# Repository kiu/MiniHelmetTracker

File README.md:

# MiniHelmetTracker

*MiniHelmetTracker* is a real-time standings table robot.

*MiniHelmetTracker* retrieves standings data - close to real-time - via WiFi and sorts [mini helmets](https://www.amazon.de/Riddell-8056173-NFL-32-teiliges-Helm-Tracker-Set/dp/B088W86SX4/) by league, conference, division or playoffs. A physical representation of the well known standings tables from [NFL](https://www.espn.com/nfl/standings) or [ESPN](https://www.espn.com/nfl/standings).

Checkout the [full story](https://schoar.de/tinkering/MiniHelmetTracker) or explore this repository including STL files, schematics, PCB layouts, firmware, server, etc.

# Youtube

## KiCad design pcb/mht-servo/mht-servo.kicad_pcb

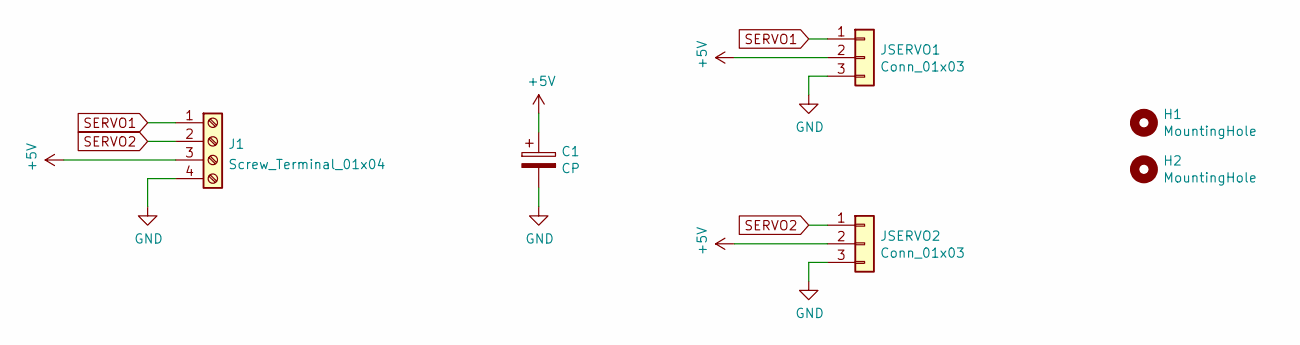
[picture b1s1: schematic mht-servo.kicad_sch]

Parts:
C1: CP; CP_Elec_8x10
H1, H2: MountingHole; MountingHole_3.2mm_M3
J1: Screw_Terminal_01x04; PinHeader_1x04_P2.54mm_Vertical
JSERVO1, JSERVO2: Conn_01x03; Pin_Header_Straight_1x03_Pitch2.54mm

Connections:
+5V: C1.1, J1.3, JSERVO1.2, JSERVO2.2
GND: C1.2, J1.4, JSERVO1.3, JSERVO2.3
SERVO1: J1.1, JSERVO1.1
SERVO2: J1.2, JSERVO2.1

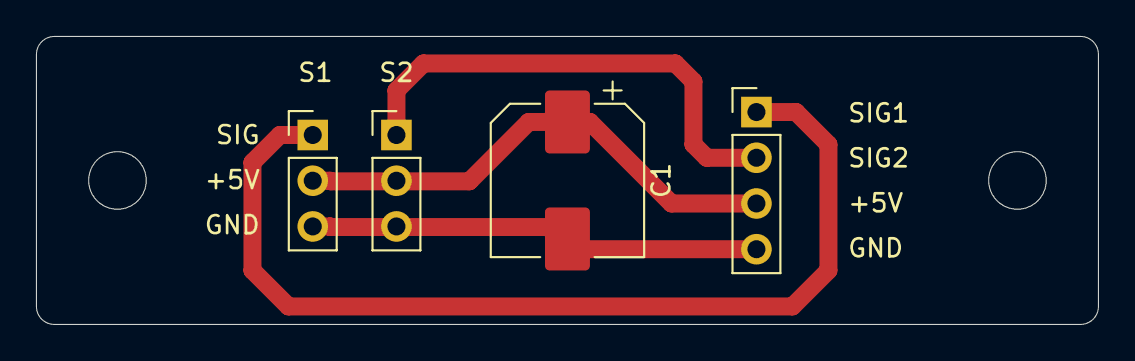
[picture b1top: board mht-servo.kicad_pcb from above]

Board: 2 copper layers, 59.0 x 16.0 mm, 6 parts (0 on the bottom side), 4 nets.

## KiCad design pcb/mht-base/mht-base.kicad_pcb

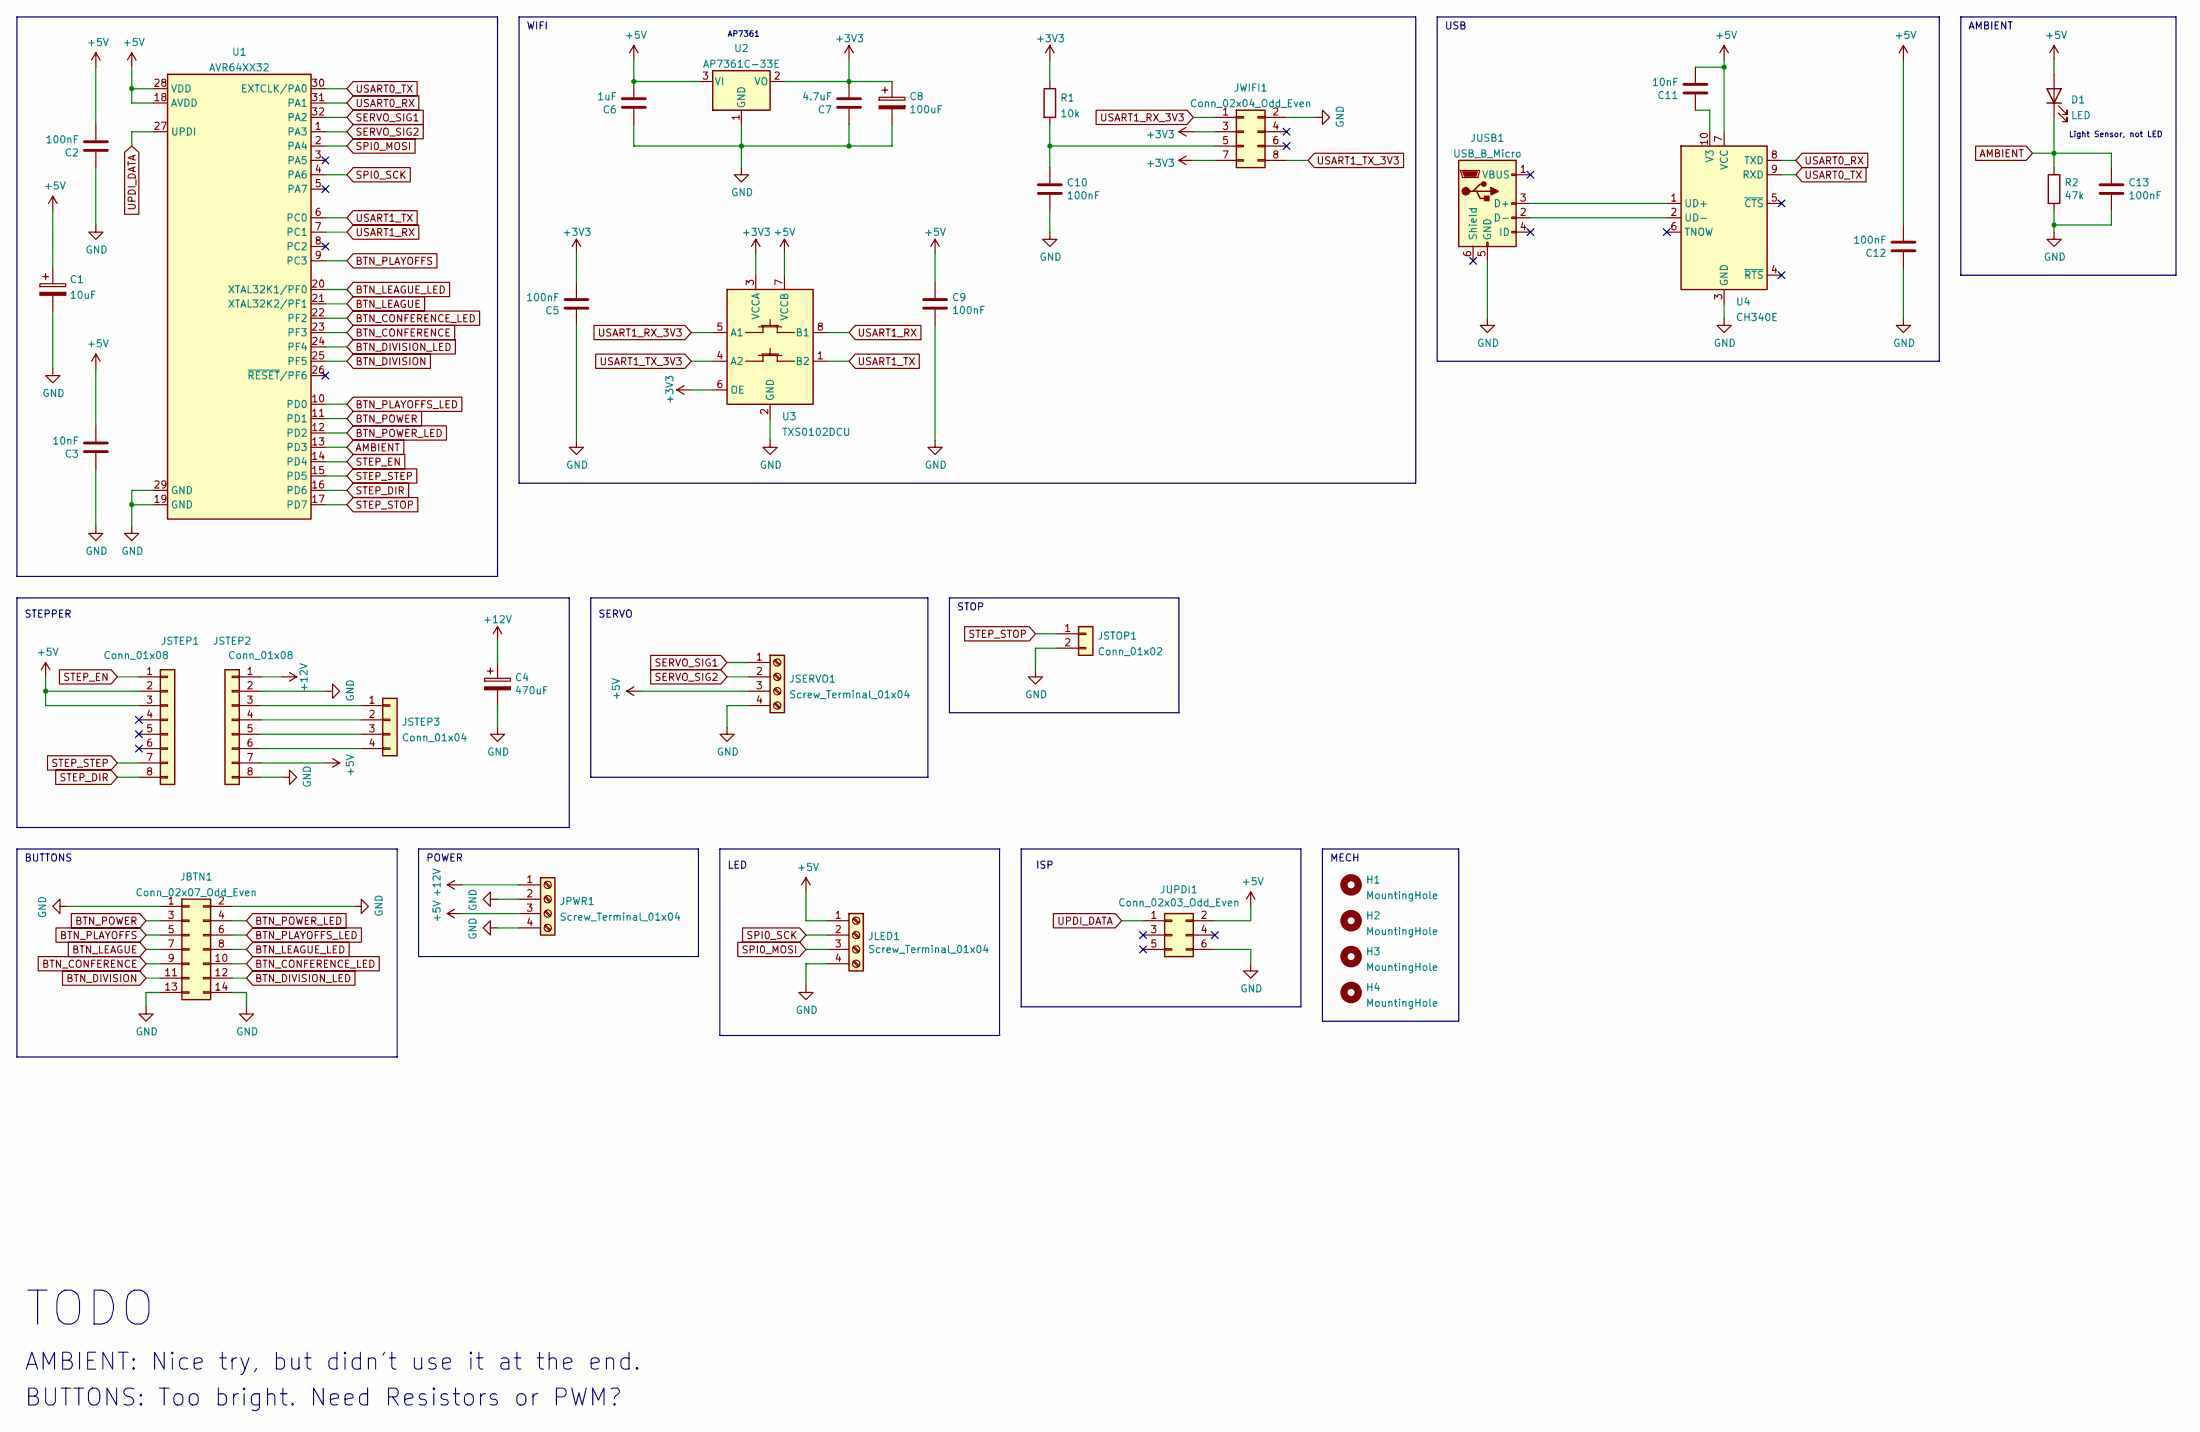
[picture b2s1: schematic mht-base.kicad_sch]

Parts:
C1: 10uF; CP_EIA-3216-18_Kemet-A
C2, C5, C9, C10, C12, C13: 100nF; C_0805_2012Metric
C3, C11: 10nF; C_0805_2012Metric
C4: 470uF; CP_Elec_8x10
C6: 1uF; C_0805_2012Metric
C7: 4.7uF; C_0805_2012Metric
C8: 100uF; CP_EIA-3528-21_Kemet-B
D1: LED; LED_D5.0mm
H1, H2, H3, H4: MountingHole; MountingHole_3.2mm_M3
JBTN1: Conn_02x07_Odd_Even; IDC-Header_2x07_P2.54mm_Vertical
JLED1: Screw_Terminal_01x04; TerminalBlock_RND_205-00047_1x04_P5.00mm_Horizontal
JPWR1: Screw_Terminal_01x04; TerminalBlock_RND_205-00047_1x04_P5.00mm_Horizontal
JSERVO1: Screw_Terminal_01x04; TerminalBlock_RND_205-00047_1x04_P5.00mm_Horizontal
JSTEP1, JSTEP2: Conn_01x08; PinSocket_1x08_P2.54mm_Vertical
JSTEP3: Conn_01x04; PinHeader_1x04_P2.54mm_Vertical
JSTOP1: Conn_01x02; TerminalBlock_RND_205-00012_1x02_P5.00mm_Horizontal
JUPDI1: Conn_02x03_Odd_Even; IDC-Header_2x03_P2.54mm_Vertical
JUSB1: USB_B_Micro; GCT-USB3076-30-A
JWIFI1: Conn_02x04_Odd_Even; PinHeader_2x04_P2.54mm_Vertical
R1: 10k; R_0805_2012Metric
R2: 47k; R_0805_2012Metric
U1: AVR64XX32; TQFP-32_7x7mm_P0.8mm
U2: AP7361C-33E; SOT-223-3_TabPin2
U3: TXS0102DCU; VSSOP-8_2.3x2mm_P0.5mm
U4: CH340E; MSOP-10_3x3mm_P0.5mm

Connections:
+3V3: C5.2, C7.2, C8.1, JWIFI1.3, JWIFI1.7, R1.1, U2.2 (VO), U3.3 (VCCA), U3.6 (OE)
+5V: C1.1, C2.2, C3.2, C6.2, C9.1, C11.2, C12.2, D1.2 (A), JLED1.1, JPWR1.3, JSERVO1.3, JSTEP1.2, JSTEP1.3, JSTEP2.7, JUPDI1.2, U1.18 (AVDD), U1.28 (VDD), U2.3 (VI), U3.7 (VCCB), U4.7 (VCC)
+12V: C4.1, JPWR1.1, JSTEP2.1
AMBIENT: C13.1, D1.1 (K), R2.1, U1.13 (PD3)
BTN_CONFERENCE: JBTN1.9, U1.23 (PF3)
BTN_CONFERENCE_LED: JBTN1.10, U1.22 (PF2)
BTN_DIVISION: JBTN1.11, U1.25 (PF5)
BTN_DIVISION_LED: JBTN1.12, U1.24 (PF4)
BTN_LEAGUE: JBTN1.7, U1.21 (XTAL32K2/PF1)
BTN_LEAGUE_LED: JBTN1.8, U1.20 (XTAL32K1/PF0)
BTN_PLAYOFFS: JBTN1.5, U1.9 (PC3)
BTN_PLAYOFFS_LED: JBTN1.6, U1.10 (PD0)
BTN_POWER: JBTN1.3, U1.11 (PD1)
BTN_POWER_LED: JBTN1.4, U1.12 (PD2)
GND: C1.2, C2.1, C3.1, C4.2, C5.1, C6.1, C7.1, C8.2, C9.2, C10.2, C12.1, C13.2, JBTN1.1, JBTN1.2, JBTN1.13, JBTN1.14, JLED1.4, JPWR1.2, JPWR1.4, JSERVO1.4, JSTEP2.2, JSTEP2.8, JSTOP1.2, JUPDI1.6, JUSB1.5 (GND), JWIFI1.2, R2.2, U1.19 (GND), U1.29 (GND), U2.1 (GND), U3.2 (GND), U4.3 (GND)
unnamed: C10.1, JWIFI1.5, R1.2
unnamed: C11.1, U4.10 (V3)
unnamed: JSTEP2.3, JSTEP3.1
unnamed: JSTEP2.4, JSTEP3.2
unnamed: JSTEP2.5, JSTEP3.3
unnamed: JSTEP2.6, JSTEP3.4
unnamed: JUSB1.2 (D-), U4.2 (UD-)
unnamed: JUSB1.3 (D+), U4.1 (UD+)
SERVO_SIG1: JSERVO1.1, U1.32 (PA2)
SERVO_SIG2: JSERVO1.2, U1.1 (PA3)
SPI0_MOSI: JLED1.3, U1.2 (PA4)
SPI0_SCK: JLED1.2, U1.4 (PA6)
STEP_DIR: JSTEP1.8, U1.16 (PD6)
STEP_EN: JSTEP1.1, U1.14 (PD4)
STEP_STEP: JSTEP1.7, U1.15 (PD5)
STEP_STOP: JSTOP1.1, U1.17 (PD7)
UPDI_DATA: JUPDI1.1, U1.27 (UPDI)
USART0_RX: U1.31 (PA1), U4.8 (TXD)
USART0_TX: U1.30 (EXTCLK/PA0), U4.9 (RXD)
USART1_RX: U1.7 (PC1), U3.8 (B1)
USART1_RX_3V3: JWIFI1.1, U3.5 (A1)
USART1_TX: U1.6 (PC0), U3.1 (B2)
USART1_TX_3V3: JWIFI1.8, U3.4 (A2)

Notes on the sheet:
TODO
USB
AMBIENT
LED
BUTTONS
STOP
WIFI
POWER
MECH
ISP
AP7361
STEPPER
AMBIENT: Nice try, but didn't use it at the end.
SERVO
Light Sensor, not LED
BUTTONS: Too bright. Need Resistors or PWM?

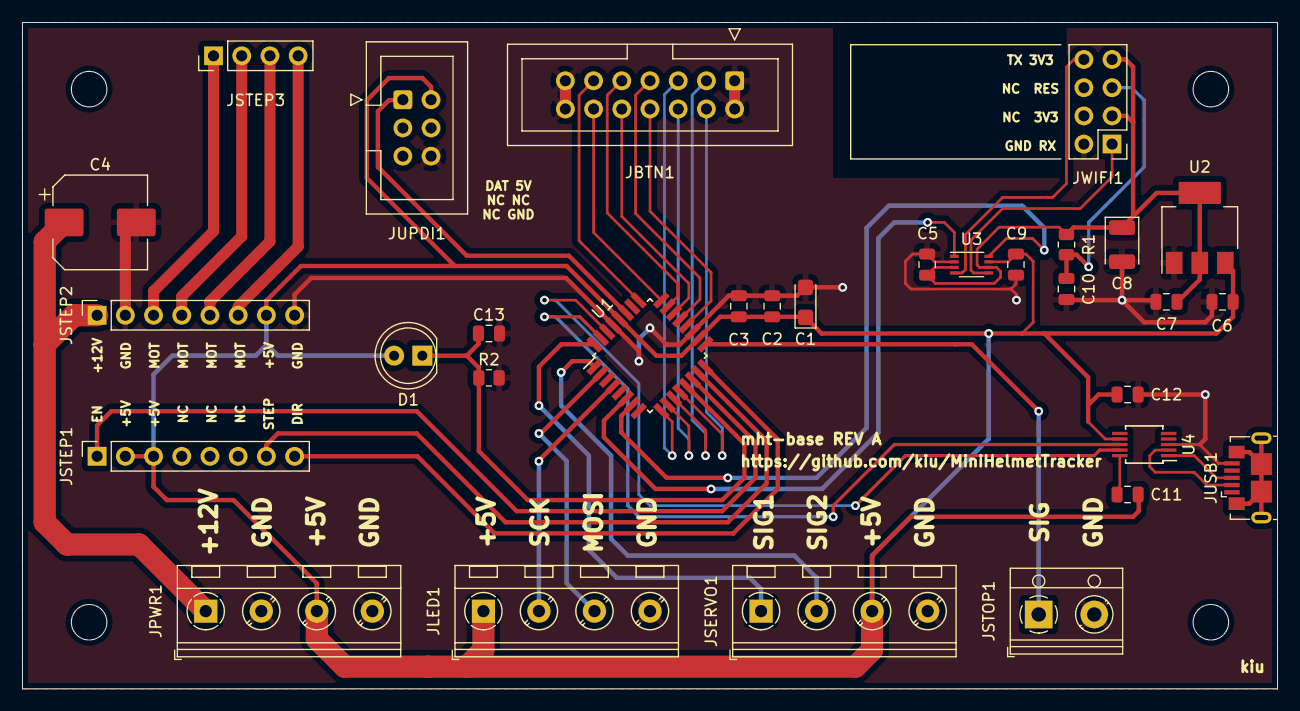
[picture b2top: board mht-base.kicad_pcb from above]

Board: 2 copper layers, 113.0 x 60.0 mm, 35 parts (0 on the bottom side), 38 nets.

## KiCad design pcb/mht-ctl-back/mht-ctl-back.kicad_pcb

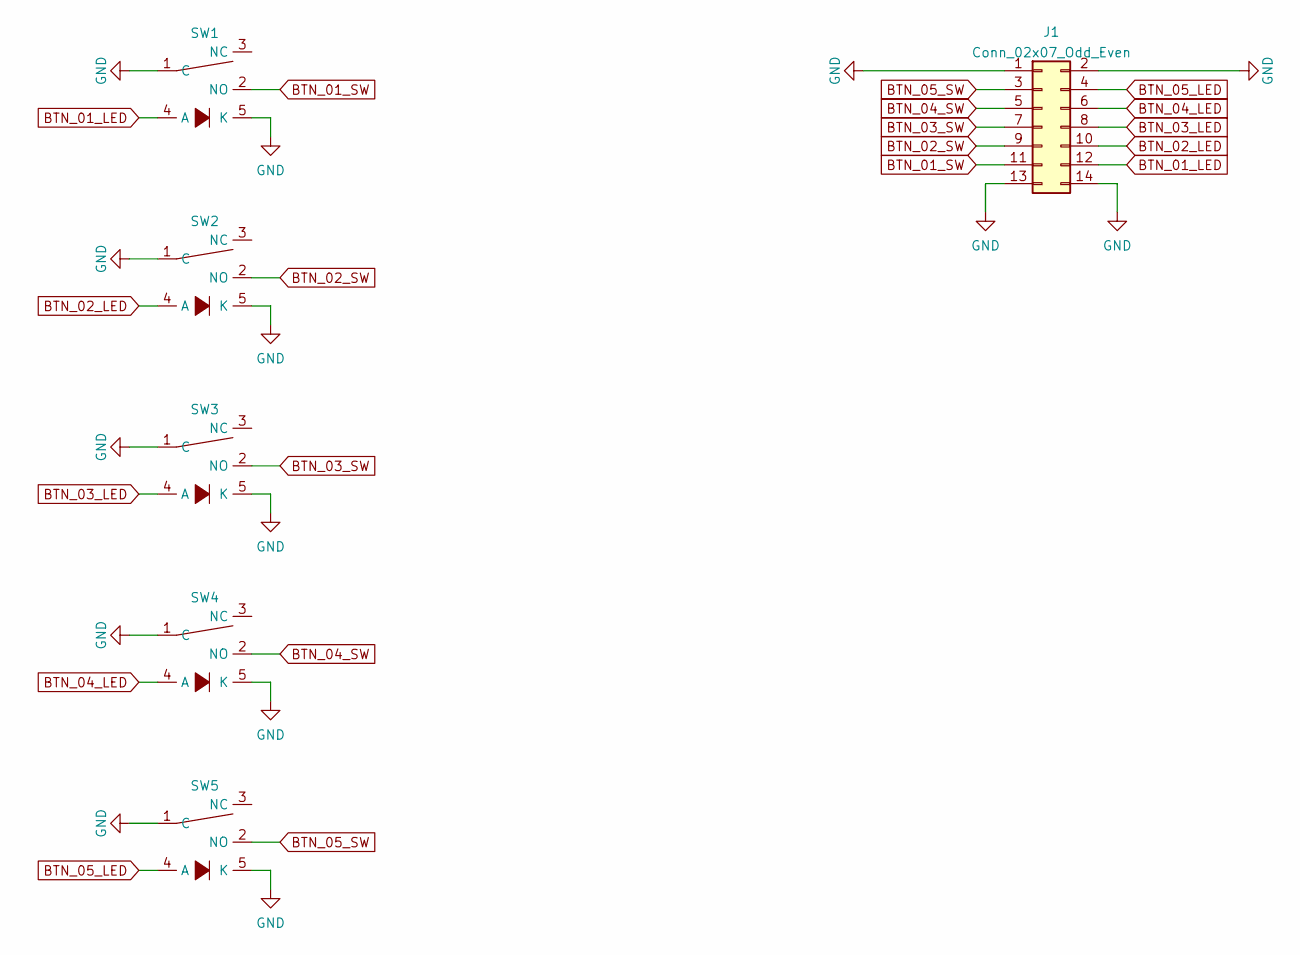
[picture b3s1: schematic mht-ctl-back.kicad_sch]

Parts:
J1: Conn_02x07_Odd_Even; IDC-Header_2x07_P2.54mm_Horizontal
SW1, SW2, SW3, SW4: PushButtonLED; PushButtonLED18
SW5: PushButtonLED; PushButtonLED24

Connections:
BTN_01_LED: J1.12, SW1.4 (A)
BTN_01_SW: J1.11, SW1.2 (NO)
BTN_02_LED: J1.10, SW2.4 (A)
BTN_02_SW: J1.9, SW2.2 (NO)
BTN_03_LED: J1.8, SW3.4 (A)
BTN_03_SW: J1.7, SW3.2 (NO)
BTN_04_LED: J1.6, SW4.4 (A)
BTN_04_SW: J1.5, SW4.2 (NO)
BTN_05_LED: J1.4, SW5.4 (A)
BTN_05_SW: J1.3, SW5.2 (NO)
GND: J1.1, J1.2, J1.13, J1.14, SW1.1 (C), SW1.5 (K), SW2.1 (C), SW2.5 (K), SW3.1 (C), SW3.5 (K), SW4.1 (C), SW4.5 (K), SW5.1 (C), SW5.5 (K)

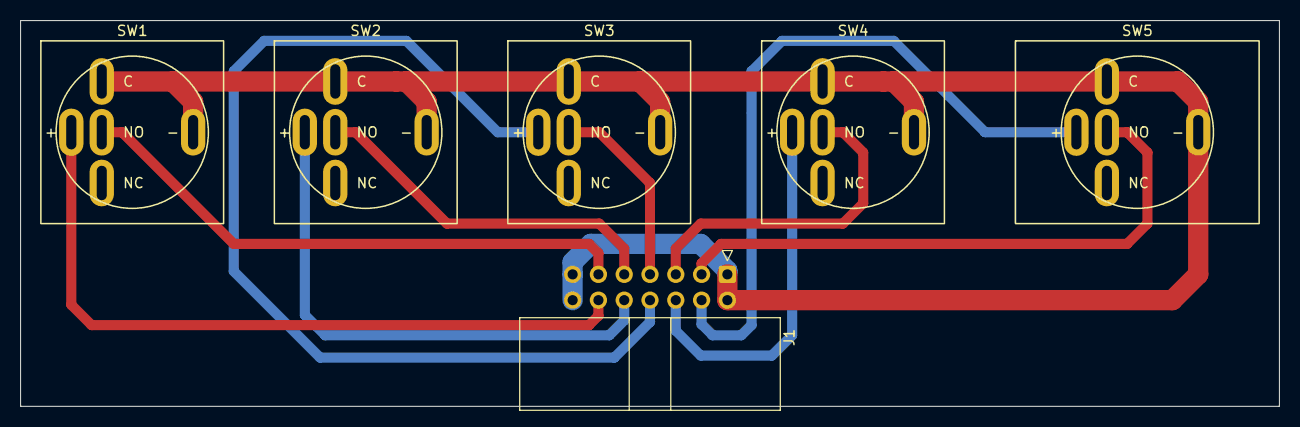
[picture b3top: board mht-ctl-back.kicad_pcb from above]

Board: 2 copper layers, 124.0 x 38.0 mm, 6 parts (0 on the bottom side), 11 nets.

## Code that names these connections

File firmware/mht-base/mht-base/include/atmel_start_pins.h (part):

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#include <port.h>

/**
 * \brief Set PA0 pull mode
 *
 * Configure pin to pull up, down or disable pull mode, supported pull
 * modes are defined by device used
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}

/**
 * \brief Set PA0 data direction
 *
 * Select if the pin data direction is input, output or disabled.
 * If disabled state is not possible, this function throws an assert.
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}

/**
 * \brief Set PA0 input/sense configuration
 *
 * Enable/disable PA0 digital input buffer and pin change interrupt,
 * select pin interrupt edge/level sensing mode
 *
 * \param[in] isc PORT_ISC_INTDISABLE_gc    = Iterrupt disabled but input buffer enabled
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}

/**
 * \brief Set PA0 inverted mode
 *
 * Enable or disable inverted I/O on a pin
 *
 * \param[in] inverted true  = I/O on PA0 is inverted
 *                     false = I/O on PA0 is not inverted
 */
static inline void PA0_set_inverted(const bool inverted)
{
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}

/**
 * \brief Set PA0 level
 *
 * Sets output level on a pin
 *
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}

/**
 * \brief Toggle output level on PA0
 *
 * Toggle the pin level
 */
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}

/**
 * \brief Get level on PA0
 *
 * Reads the level on a pin
 */
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}

/**
 * \brief Set PA1 pull mode
 *
 * Configure pin to pull up, down or disable pull mode, supported pull
 * modes are defined by device used
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}

/**
 * \brief Set PA1 data direction
 *
 * Select if the pin data direction is input, output or disabled.
 * If disabled state is not possible, this function throws an assert.
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}

/**
 * \brief Set PA1 input/sense configuration
 *
 * Enable/disable PA1 digital input buffer and pin change interrupt,
 * select pin interrupt edge/level sensing mode
 *
 * \param[in] isc PORT_ISC_INTDISABLE_gc    = Iterrupt disabled but input buffer enabled
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}

/**
 * \brief Set PA1 inverted mode
 *
 * Enable or disable inverted I/O on a pin
 *
 * \param[in] inverted true  = I/O on PA1 is inverted
 *                     false = I/O on PA1 is not inverted
 */
static inline void PA1_set_inverted(const bool inverted)
{
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}

/**
 * \brief Set PA1 level
 *
 * Sets output level on a pin
 *
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}

/**
 * \brief Toggle output level on PA1
 *
 * Toggle the pin level
 */
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}

/**
 * \brief Get level on PA1
 *
 * Reads the level on a pin
 */
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/**
 * \brief Set SERVO_SIG1 input/sense configuration
 *
 * Enable/disable SERVO_SIG1 digital input buffer and pin change interrupt,
 * select pin interrupt edge/level sensing mode
 *
 * \param[in] isc PORT_ISC_INTDISABLE_gc    = Iterrupt disabled but input buffer enabled
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/**
 * \brief Set SERVO_SIG2 input/sense configuration
 *
 * Enable/disable SERVO_SIG2 digital input buffer and pin change interrupt,
 * select pin interrupt edge/level sensing mode
 *
 * \param[in] isc PORT_ISC_INTDISABLE_gc    = Iterrupt disabled but input buffer enabled
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}

/**
 * \brief Set PA4 pull mode
 *
 * Configure pin to pull up, down or disable pull mode, supported pull
 * modes are defined by device used
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}

/**
 * \brief Set PA4 data direction
 *
 * Select if the pin data direction is input, output or disabled.
 * If disabled state is not possible, this function throws an assert.
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}

/**
 * \brief Set PA4 input/sense configuration
 *
 * Enable/disable PA4 digital input buffer and pin change interrupt,
 * select pin interrupt edge/level sensing mode
 *
 * \param[in] isc PORT_ISC_INTDISABLE_gc    = Iterrupt disabled but input buffer enabled
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}

/**
 * \brief Set PA4 inverted mode
 *
 * Enable or disable inverted I/O on a pin
 *
 * \param[in] inverted true  = I/O on PA4 is inverted
 *                     false = I/O on PA4 is not inverted
 */
static inline void PA4_set_inverted(const bool inverted)
{
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}

/**
 * \brief Set PA4 level
 *
 * Sets output level on a pin
 *
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}

/**
 * \brief Toggle output level on PA4
 *
 * Toggle the pin level
 */
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}

/**
 * \brief Get level on PA4
 *
 * Reads the level on a pin
 */
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}

/**
 * \brief Set PA6 pull mode
 *
 * Configure pin to pull up, down or disable pull mode, supported pull
 * modes are defined by device used
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}

/**
 * \brief Set PA6 data direction
 *
 * Select if the pin data direction is input, output or disabled.
 * If disabled state is not possible, this function throws an assert.
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}

/**
 * \brief Set PA6 input/sense configuration
 *
 * Enable/disable PA6 digital input buffer and pin change interrupt,
 * select pin interrupt edge/level sensing mode
 *
 * \param[in] isc PORT_ISC_INTDISABLE_gc    = Iterrupt disabled but input buffer enabled
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}

/**
 * \brief Set PA6 inverted mode
 *
 * Enable or disable inverted I/O on a pin
 *
 * \param[in] inverted true  = I/O on PA6 is inverted
 *                     false = I/O on PA6 is not inverted
 */
static inline void PA6_set_inverted(const bool inverted)
{
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}

/**
 * \brief Set PA6 level
 *
 * Sets output level on a pin
 *
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}

/**
 * \brief Toggle output level on PA6
 *
 * Toggle the pin level
 */
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}

/**
 * \brief Get level on PA6
 *
 * Reads the level on a pin
 */
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}

/**
 * \brief Set PC0 pull mode
 *
 * Configure pin to pull up, down or disable pull mode, supported pull
 * modes are defined by device used
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}

/**
 * \brief Set PC0 data direction
 *
 * Select if the pin data direction is input, output or disabled.
 * If disabled state is not possible, this function throws an assert.
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}

/**
 * \brief Set PC0 input/sense configuration
 *
 * Enable/disable PC0 digital input buffer and pin change interrupt,
 * select pin interrupt edge/level sensing mode
 *
 * \param[in] isc PORT_ISC_INTDISABLE_gc    = Iterrupt disabled but input buffer enabled
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}

/**
 * \brief Set PC0 inverted mode
 *
 * Enable or disable inverted I/O on a pin
 *
 * \param[in] inverted true  = I/O on PC0 is inverted
 *                     false = I/O on PC0 is not inverted
 */
static inline void PC0_set_inverted(const bool inverted)
{
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}

/**
 * \brief Set PC0 level
 *
 * Sets output level on a pin
 *
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}

/**
 * \brief Toggle output level on PC0
 *
 * Toggle the pin level
 */
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}

/**
 * \brief Get level on PC0
 *
 * Reads the level on a pin
 */
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}

/**
 * \brief Set PC1 pull mode
 *
 * Configure pin to pull up, down or disable pull mode, supported pull
 * modes are defined by device used
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}

/**
 * \brief Set PC1 data direction
 *
 * Select if the pin data direction is input, output or disabled.
 * If disabled state is not possible, this function throws an assert.
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}

/**
 * \brief Set PC1 input/sense configuration
 *
 * Enable/disable PC1 digital input buffer and pin change interrupt,
 * select pin interrupt edge/level sensing mode
 *
 * \param[in] isc PORT_ISC_INTDISABLE_gc    = Iterrupt disabled but input buffer enabled
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}

/**
 * \brief Set PC1 inverted mode
 *
 * Enable or disable inverted I/O on a pin
 *
 * \param[in] inverted true  = I/O on PC1 is inverted
 *                     false = I/O on PC1 is not inverted
 */
static inline void PC1_set_inverted(const bool inverted)
{
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}

/**
 * \brief Set PC1 level
 *
 * Sets output level on a pin
 *
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}

/**
 * \brief Toggle output level on PC1
 *
 * Toggle the pin level
 */
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}

/**
 * \brief Get level on PC1
 *
 * Reads the level on a pin
 */
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/**
 * \brief Set BTN_PLAYOFFS input/sense configuration
 *
 * Enable/disable BTN_PLAYOFFS digital input buffer and pin change interrupt,
 * select pin interrupt edge/level sensing mode
 *
 * \param[in] isc PORT_ISC_INTDISABLE_gc    = Iterrupt disabled but input buffer enabled
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/**
 * \brief Set BTN_PLAYOFFS_LED input/sense configuration
 *
 * Enable/disable BTN_PLAYOFFS_LED digital input buffer and pin change interrupt,
 * select pin interrupt edge/level sensing mode
 *
 * \param[in] isc PORT_ISC_INTDISABLE_gc    = Iterrupt disabled but input buffer enabled
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/**
 * \brief Set BTN_POWER input/sense configuration
 *
 * Enable/disable BTN_POWER digital input buffer and pin change interrupt,
 * select pin interrupt edge/level sensing mode
 *
 * \param[in] isc PORT_ISC_INTDISABLE_gc    = Iterrupt disabled but input buffer enabled
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/**
 * \brief Set BTN_POWER_LED input/sense configuration
 *
 * Enable/disable BTN_POWER_LED digital input buffer and pin change interrupt,
 * select pin interrupt edge/level sensing mode
 *
 * \param[in] isc PORT_ISC_INTDISABLE_gc    = Iterrupt disabled but input buffer enabled
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/**
 * \brief Set STEP_EN input/sense configuration
 *
 * Enable/disable STEP_EN digital input buffer and pin change interrupt,
 * select pin interrupt edge/level sensing mode
 *
 * \param[in] isc PORT_ISC_INTDISABLE_gc    = Iterrupt disabled but input buffer enabled
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/**
 * \brief Set STEP_STEP input/sense configuration
 *
 * Enable/disable STEP_STEP digital input buffer and pin change interrupt,
 * select pin interrupt edge/level sensing mode
 *
 * \param[in] isc PORT_ISC_INTDISABLE_gc    = Iterrupt disabled but input buffer enabled
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/**
 * \brief Set STEP_DIR input/sense configuration
 *
 * Enable/disable STEP_DIR digital input buffer and pin change interrupt,
 * select pin interrupt edge/level sensing mode
 *
 * \param[in] isc PORT_ISC_INTDISABLE_gc    = Iterrupt disabled but input buffer enabled
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/**
 * \brief Set STEP_STOP input/sense configuration
 *
 * Enable/disable STEP_STOP digital input buffer and pin change interrupt,
 * select pin interrupt edge/level sensing mode
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
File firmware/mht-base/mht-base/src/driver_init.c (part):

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{
	mcu_init();

	/* PORT setting on PC3 */

	BTN_PLAYOFFS_set_level(
	    // <y> Initial level
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	    // <PORT_ISC_LEVEL_gc"> Sense low Level
	    PORT_ISC_FALLING_gc);

	/* PORT setting on PD0 */

	// Set pin direction to output

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
	BTN_PLAYOFFS_LED_set_dir(PORT_DIR_OUT);

	/* PORT setting on PD1 */

	BTN_POWER_set_level(
	    // <y> Initial level
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	    // <PORT_ISC_LEVEL_gc"> Sense low Level
	    PORT_ISC_FALLING_gc);

	/* PORT setting on PD2 */

	// Set pin direction to output

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
	BTN_POWER_LED_set_dir(PORT_DIR_OUT);

	/* PORT setting on PD4 */

	// Set pin direction to output

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
	STEP_EN_set_dir(PORT_DIR_OUT);

	/* PORT setting on PD5 */

	// Set pin direction to output

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
	STEP_STEP_set_dir(PORT_DIR_OUT);

	/* PORT setting on PD6 */

	// Set pin direction to output

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
	STEP_DIR_set_dir(PORT_DIR_OUT);

	/* PORT setting on PD7 */

	// Set pin direction to input
	STEP_STOP_set_dir(PORT_DIR_IN);
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	    // <PORT_PULL_UP"> Pull-up
	    PORT_PULL_UP);

	/* PORT setting on PF0 */

	// Set pin direction to output

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
	BTN_LEAGUE_LED_set_dir(PORT_DIR_OUT);

	/* PORT setting on PF1 */

	BTN_LEAGUE_set_level(
	    // <y> Initial level
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	    // <PORT_ISC_LEVEL_gc"> Sense low Level
	    PORT_ISC_FALLING_gc);

	/* PORT setting on PF2 */

	// Set pin direction to output

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
	BTN_CONFERENCE_LED_set_dir(PORT_DIR_OUT);

	/* PORT setting on PF3 */

	BTN_CONFERENCE_set_level(
	    // <y> Initial level
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	    // <PORT_ISC_LEVEL_gc"> Sense low Level
	    PORT_ISC_FALLING_gc);

	/* PORT setting on PF4 */

	// Set pin direction to output

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
	BTN_DIVISION_LED_set_dir(PORT_DIR_OUT);

	/* PORT setting on PF5 */

	BTN_DIVISION_set_level(
	    // <y> Initial level
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
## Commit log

2022-08-12 Initial files.
2022-08-12 Initial server
2022-08-12 BOM and texts
2022-08-13 Need some waiting perios for servo to reach end position.
2022-08-14 Turn buttons off when leds are off
2022-08-15 Prepare public release...
2022-08-15 Bigger youtube thumbnail
2022-08-15 Readme cleanup
2022-08-16 Adding Making Of video
2022-08-19 35W model is good enough
2022-09-08 Scores are null in case game didn't happen yet. Ignore those. If playoff didn't start yet, download is 400. Ignore this.
2022-09-11 Live data is available on a different endpoint Admin interface to control polling Multiple off-by-ones More debug output
2022-09-13 Use proper TimeZone for sleep period Another off-by-one

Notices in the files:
firmware/mht-base/mht-base/src/driver_init.c:
(c) 2020 Microchip Technology Inc. and its subsidiaries.
